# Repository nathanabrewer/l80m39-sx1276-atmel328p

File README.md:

# l80m39-sx1276-atmel328p

Major Parts in Build v0.1
- sx1276 HopeRF/NiceRD RFM95/RFM96	~ $5.49	(aliexpress)	
- l80m39 GPS Radio	~5.99	
- ATMEGA328P-AU ~ $3.00 (digikey)
- PCB Board ~ $2.00 

Basic Build < $20 each.

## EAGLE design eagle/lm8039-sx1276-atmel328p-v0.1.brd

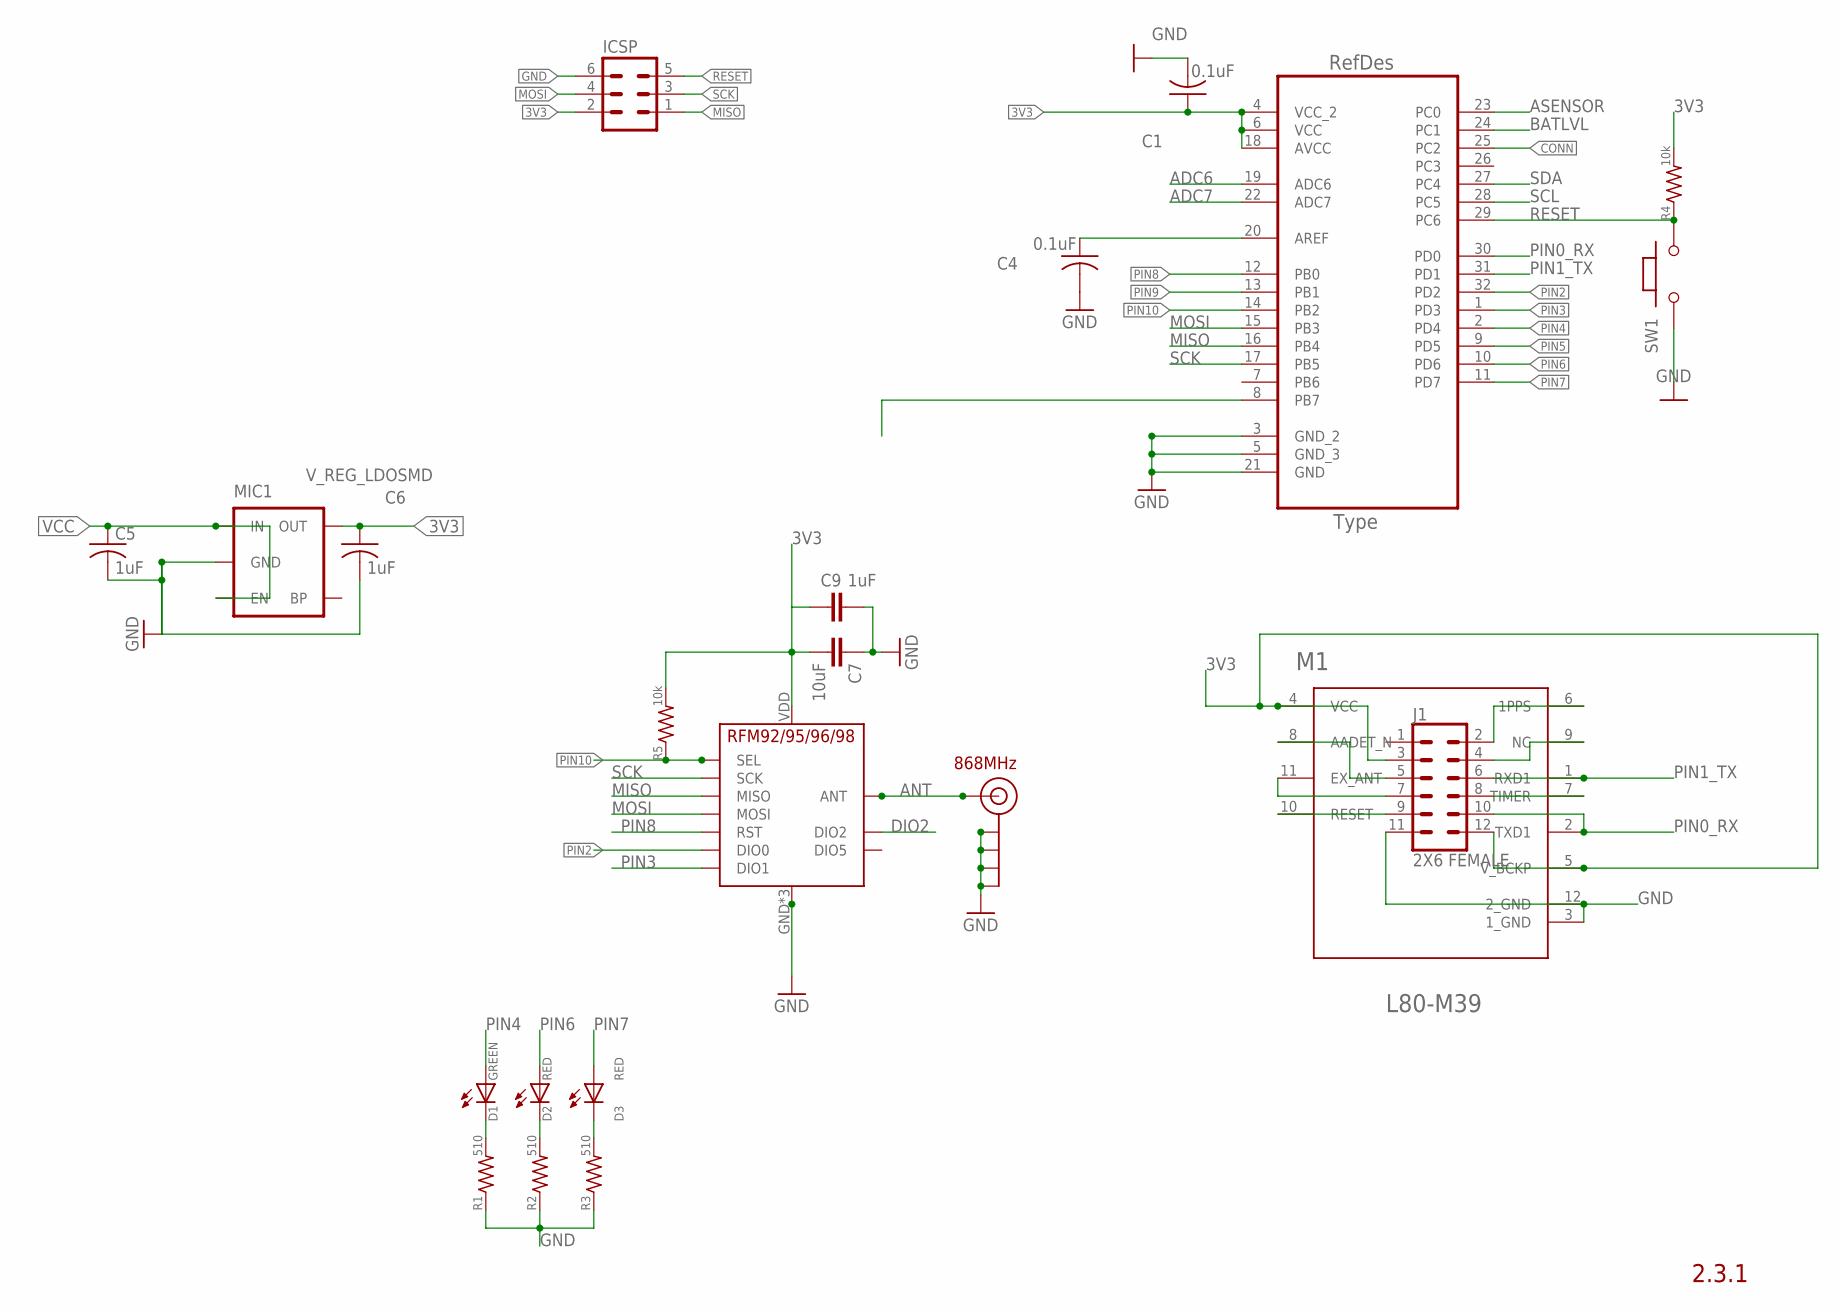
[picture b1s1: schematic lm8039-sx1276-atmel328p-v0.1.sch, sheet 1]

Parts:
C1, C4: 0.1uF; C0805
C5, C6: 1uF; C0805
C7: 10uF; 0805-CAP-LARGEPADS
C9: 1uF; 0805-CAP-LARGEPADS
D1: GREEN; LED0603
D2, D3: RED; LED0603
ICSP: MA03-2
J1: 2X6 FEMALE; 2X6
J$2: ANTENNATINY; SMA_UFL_PAD_TINY
M1: QUECTEL_L80-M39QUECTEL_L80-M39_0_0; QUECTEL_L80-M39_0
MIC1: V_REG_LDOSMD; SOT23-5
R1, R2, R3: 510; R0603
R4, R5: 10k; R0603
SW1: RESET; SMD_157SW
U1: ATMEGA328P-AU; QFP80P900X900X120-32N
U$5: RFM95

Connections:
3V3: C1.1, C6.1, C7.2, C9.2, ICSP.2, J1.3, J1.12, M1.4 (VCC), M1.5 (V_BCKP), MIC1.5 (OUT), R4.2, R5.2, U1.4 (VCC_2), U1.6 (VCC), U1.18 (AVCC), U$5.VDD (VCC)
ADC6: U1.19 (ADC6)
ADC7: U1.22 (ADC7)
ANT: J$2.ANT1 (SIGNAL), J$2.ANT2 (SIGNAL), J$2.ANT3 (SIGNAL), U$5.ANT
ASENSOR: U1.23 (PC0)
BATLVL: U1.24 (PC1)
CONN: U1.25 (PC2)
DIO2: U$5.DIO2
GND: C1.2, C4.2, C5.2, C6.2, C7.1, C9.1, ICSP.6, J1.11, J$2.GND1 (GND), J$2.GND2 (GND), J$2.GND3 (GND), J$2.GND4 (GND), M1.3 (1_GND), M1.12 (2_GND), MIC1.2 (GND), R1.1, R2.1, R3.1, SW1.1, U1.3 (GND_2), U1.5 (GND_3), U1.21 (GND), U$5.GND, U$5.GND1 (GND), U$5.GND2 (GND)
MISO: ICSP.1, U1.16 (PB4), U$5.MISO
MOSI: ICSP.4, U1.15 (PB3), U$5.MOSI
unnamed: D3.C, R3.2
unnamed: C4.1, U1.20 (AREF)
unnamed: J1.2, M1.6 (1PPS)
unnamed: J1.4, M1.9 (NC)
unnamed: J1.8, M1.7 (TIMER)
unnamed: D1.C, R1.2
unnamed: D2.C, R2.2
unnamed: J1.9, M1.10 (RESET)
unnamed: J1.7, M1.11 (EX_ANT)
unnamed: J1.5, M1.8 (AADET_N)
PIN0_RX: J1.10, M1.2 (TXD1), U1.30 (PD0)
PIN1_TX: J1.6, M1.1 (RXD1), U1.31 (PD1)
PIN2: U1.32 (PD2), U$5.DIO0
PIN3: U1.1 (PD3), U$5.DIO1
PIN4: D1.A, U1.2 (PD4)
PIN5: U1.9 (PD5)
PIN6: D2.A, U1.10 (PD6)
PIN7: D3.A, U1.11 (PD7)
PIN8: U1.12 (PB0), U$5.RST
PIN9: U1.13 (PB1)
PIN10: R5.1, U1.14 (PB2), U$5.NSS (SEL)
RESET: ICSP.5, R4.1, SW1.2, U1.29 (PC6)
SCK: ICSP.3, U1.17 (PB5), U$5.SCK
SCL: U1.28 (PC5)
SDA: U1.27 (PC4)
VCC: C5.1, MIC1.1 (IN), MIC1.3 (EN)

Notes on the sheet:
2.3.1
868MHz

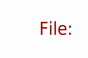
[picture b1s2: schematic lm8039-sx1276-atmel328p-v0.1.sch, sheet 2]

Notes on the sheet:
File:

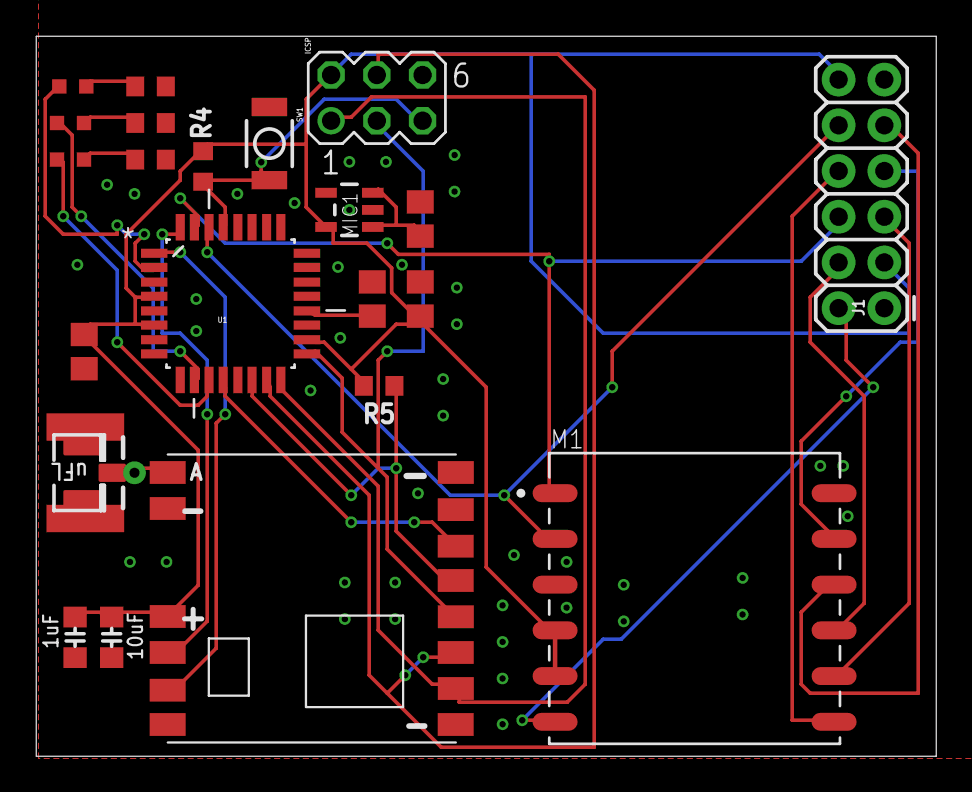
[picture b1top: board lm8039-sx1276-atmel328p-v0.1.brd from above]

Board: 2 copper layers, 50.0 x 40.0 mm, 22 parts (0 on the bottom side), 27 nets.

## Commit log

2019-08-31 Added Schematics and Arduino Code

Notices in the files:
parts and their libraries:
SparkFun: Licensing: CC v3.0 Share-Alike You are welcome to use this library for commercial purposes.
SparkFun-Connectors: Licensing: Creative Commons ShareAlike 4.0 International - https://creativecommons.org/licenses/by-sa/4.0
